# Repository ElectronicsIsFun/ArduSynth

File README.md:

ArduSynth
=========

Arduino analog synthesizer shield.

A collaborative project between Electronics is Fun and uCHobby

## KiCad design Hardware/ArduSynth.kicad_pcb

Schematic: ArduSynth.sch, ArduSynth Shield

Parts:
C1, C2: 0.1UF; C1; Part Number 594-K104K15X7RF5UH5
C3: 0.01UF; C1; Part Number 594-K103K15X7RF5UH5
D1: LED_T3_GREEN; LED-3MM; Part Number 696-SSFLX453LGD99
J1, J2: STEREO_JACK_3.5MM; JACK_3.5mm; Part Number 502-35RASMT4BHNTRX
R1: 3.3K; R4; Part Number 660-MF1/4LCT52R332J
R2: 330; R4; Part Number 660-MF1/4LCT52R331J
R3: 270; R4; Part Number 660-MF1/4LCT52R271J
R4: 100; R4; Part Number 660-MF1/4LCT52R101J
RV1, RV2, RV3, RV4, RV5, RV6: POT10K; POT_CMS; Part Number 688-RK09K1130A5R
SW1: SW_12X12MM; SW_PUSH_SMALL; Part Number 101-TS6211T2602AC-EV
U1: ARDUINOR3; ArduinoR3

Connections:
/ADJ1: RV1.2, U1.14 (A5)
/ADJ2: RV2.2, U1.13 (A4)
/ADJ3: RV3.2, U1.12 (A3)
/ADJ4: RV4.2, U1.11 (A2)
/ADJ5: RV5.2, U1.10 (A1)
/AUDIO OUT: J2.2 (TIP), J2.3 (RING), RV6.2
/CV: J1.2 (TIP), J1.3 (RING), R1.1
/TRIGGER: SW1.1, SW1.2, U1.17 (D2)
unnamed: D1.1 (A), R2.2
unnamed: C3.1, R4.2, RV6.3
unnamed: C1.1, R1.2, U1.9 (A0)
unnamed: R3.1, U1.24 (D9)
unnamed: D1.2 (K), U1.28 (D13)
unnamed: C2.1, R3.2, R4.1
VDD: R2.1, RV1.3, RV2.3, RV3.3, RV4.3, RV5.3, U1.5 (5V)
VSS: C1.2, C2.2, C3.2, J1.1 (SLEEVE), J2.1 (SLEEVE), RV1.1, RV2.1, RV3.1, RV4.1, RV5.1, RV6.1, U1.6 (GND), U1.7 (GND)

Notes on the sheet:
LFO
SWITCH CAP MOUSER 101-0219-EV COLOR BLUE

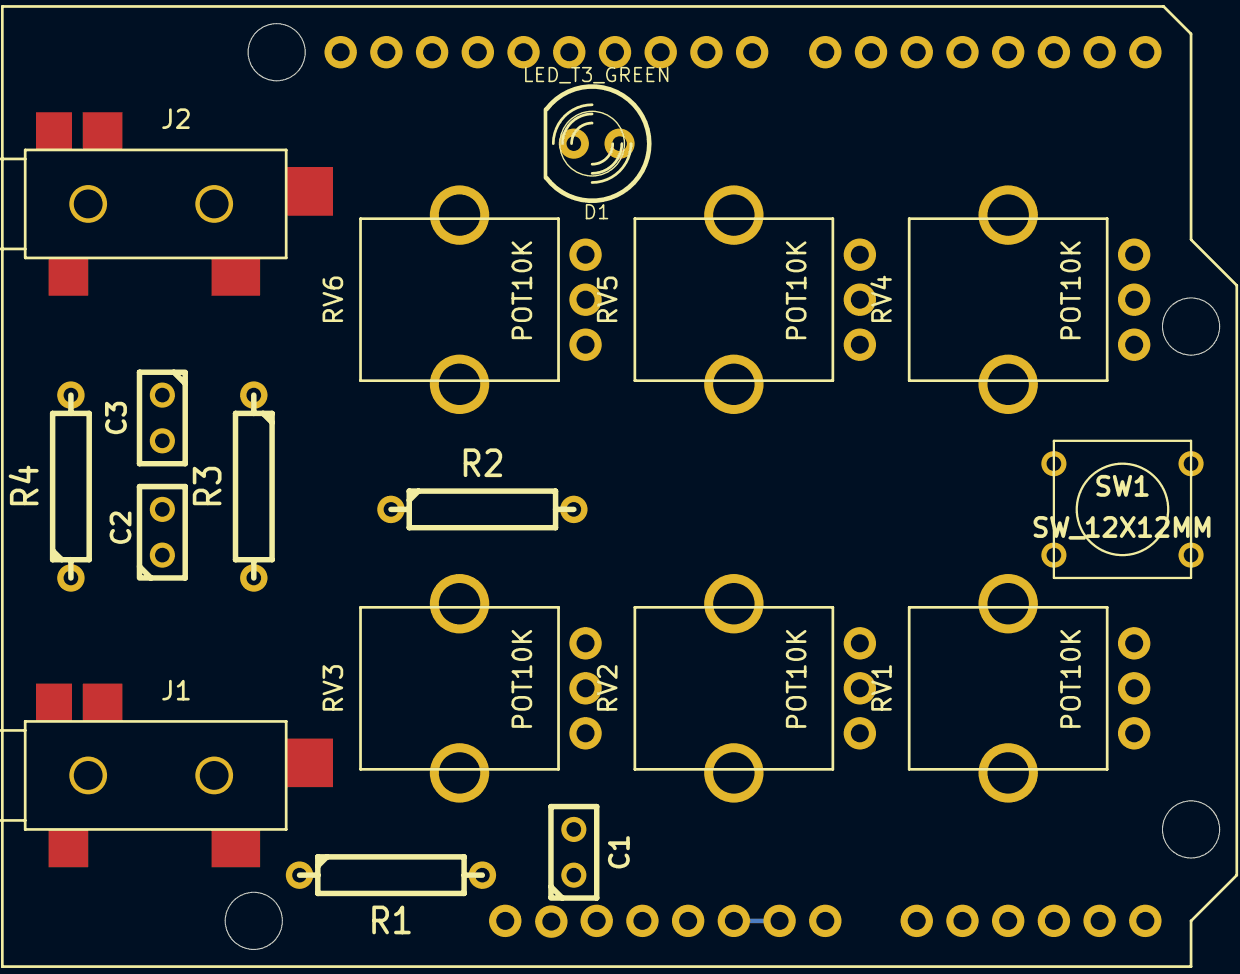
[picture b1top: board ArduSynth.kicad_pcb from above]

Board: 2 copper layers, 18 parts (0 on the bottom side), 16 nets.

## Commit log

2014-11-30 Initial File commit
2014-12-01 Added exclude for .bak
2014-12-01 Removed *.bak
2014-12-01 Removed unused exclusions
2014-12-01 Adding missing files
2014-12-01 Fixed lables on sch
2015-01-11 Updated symbols for Arduino and placement
2015-01-13 Just testing access with a minor change to the readme.
